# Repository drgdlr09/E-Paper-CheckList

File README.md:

# E-Paper CheckList - A Brief Overview
For the final week of Half-Life, I decided to design the E-Paper CheckList, a simple to-do list device with a 2.9" e-paper screen and three buttons. As a student with a lot of my plate right now, I built the CheckList in order to stay more organized and make sure I get everything I need to do done. I chose e-paper over other types of screens because it keeps showing the list even with no power, meaning the device is power-efficient and can last for a long time on one charge. You can scroll through the list using the buttons and check off items as you complete them.

# How it Works
The E-Paper Checklist has a XIAO ESP32-S3 microcontroller, a 2.9" e-paper screen for showing the list, three buttons (UP, OK and DOWN) for moving through the list and checking items off, a LiPo battery with an SS12D00 on/off switch, and a voltage divider for reading the battery level.

The E-Paper Checklist is built around the Seeed XIAO ESP32-S3, the same microcontroller I used in my Virtual SandBox. I picked it because it has a built-in battery charger and a deep sleep mode that uses almost nearly no power.

The buttons each have a 10k pull-up resistor and are wired between a GPIO pin and ground. The UP button is on D0, OK is on D1, and DOWN is on D2. I put them on these pins on purpose, because only certain pins can wake the ESP32 from deep sleep. UP and DOWN move the highlight through the list, and OK checks or unchecks the highlighted item. Holding DOWN for 1.5 seconds unchecks everything so I can start over the next day.

The e-paper screen talks to the XIAO over SPI. The screen’s SCL pin goes to D8, SDA goes to D10, CS goes to D4, DC goes to D5, RES goes to D6, and BUSY goes to D7. The screen solders straight onto a 1x8 header on the front of the board, so I don’t need any wires. The screen shows up to 6 items per page, with a header that shows how many items are done and the battery percentage.

The battery is set up the same way as my Virtual SandBox. The positive wire goes into the BAT+IN pad, through the on/off switch, out the BAT+OUT pad, and then by wire to the BAT+ pad under the XIAO. The negative wire goes straight to BAT-. The XIAO charges the battery when it’s plugged into USB-C. Two 100k resistors cut the battery voltage in half so D3 can read it, which is how the screen shows the battery percentage. The resistors are after the switch, so they don’t drain the battery when it’s turned off.

# The Firmware
The firmware is written in Arduino C++ and uses the GxEPD2 library for the e-paper screen. After 4 seconds with no button presses, the device will enter sleep mode. Pressing any button will automatically take the device out of sleep mode. The button you press to exit sleep mode matters because as soon as you press that button, the associated action will be triggered automatically.

The list is hardcoded in the firmware, so it is not editable until you change the actual code. In the future, I want to create some sort of app or webpage that allows you to update a schedule from another device, like a smartphone.

# Bill of Materials
| Part | Quantity | Unit Price | Total | Vendor |
| --- | --- | --- | --- | --- |
| 3.7V LiPo Battery | 1 | 1.06 | 1.06 | AliExpress |
| XIAO ESP32-S3 | 1 | 6.83 | 6.83 | AliExpress |
| 2.9" E-Paper Screen | 1 | 14.22 | 14.22 | AliExpress |
| PCB | 1 | 1.75 | 1.75 | JLCPCB |

TOTAL PRICE (INCLUDING $6.56 SHIPPING/TAX): $30.42
*NOTE: Other parts are needed for this project (buttons, capacitors, resistors, switches), but I either already have them or will have extras after purchasing them as part of another week.

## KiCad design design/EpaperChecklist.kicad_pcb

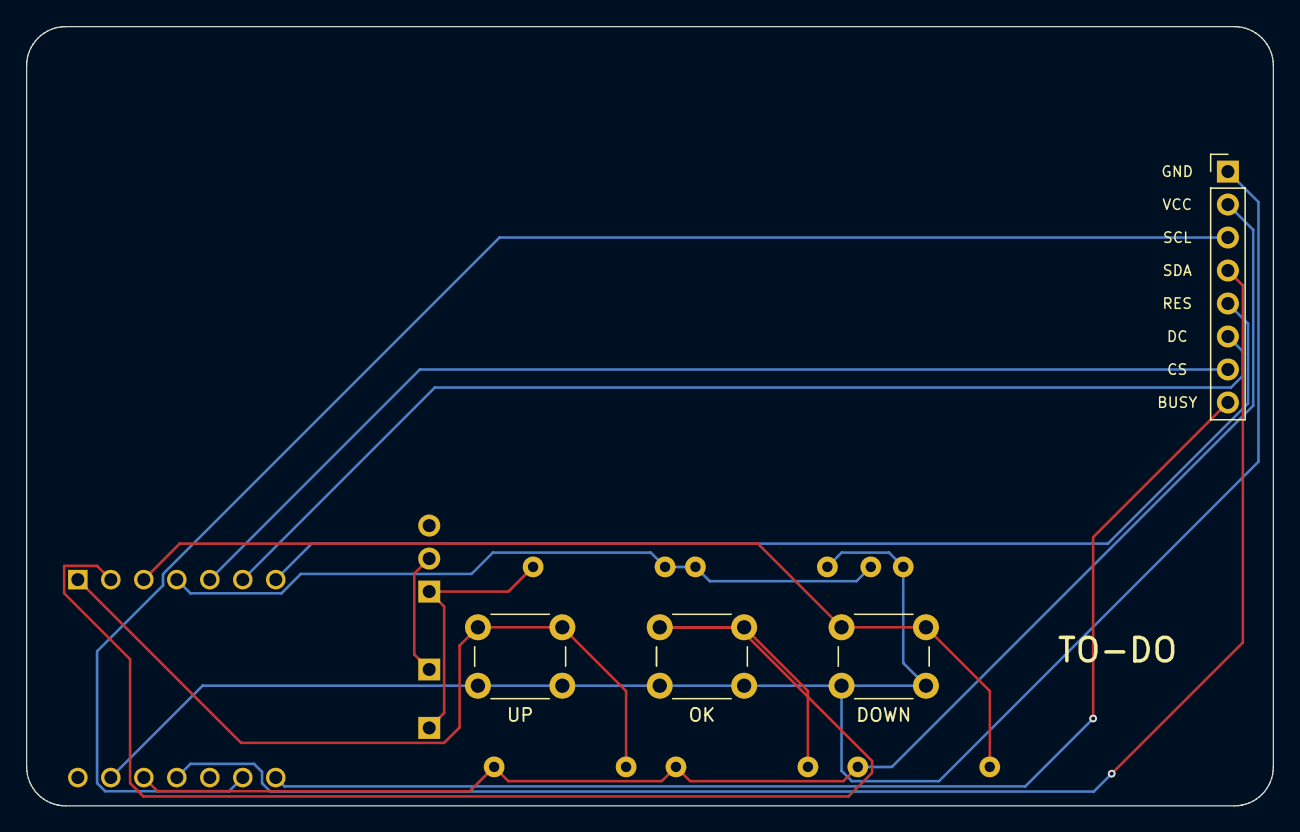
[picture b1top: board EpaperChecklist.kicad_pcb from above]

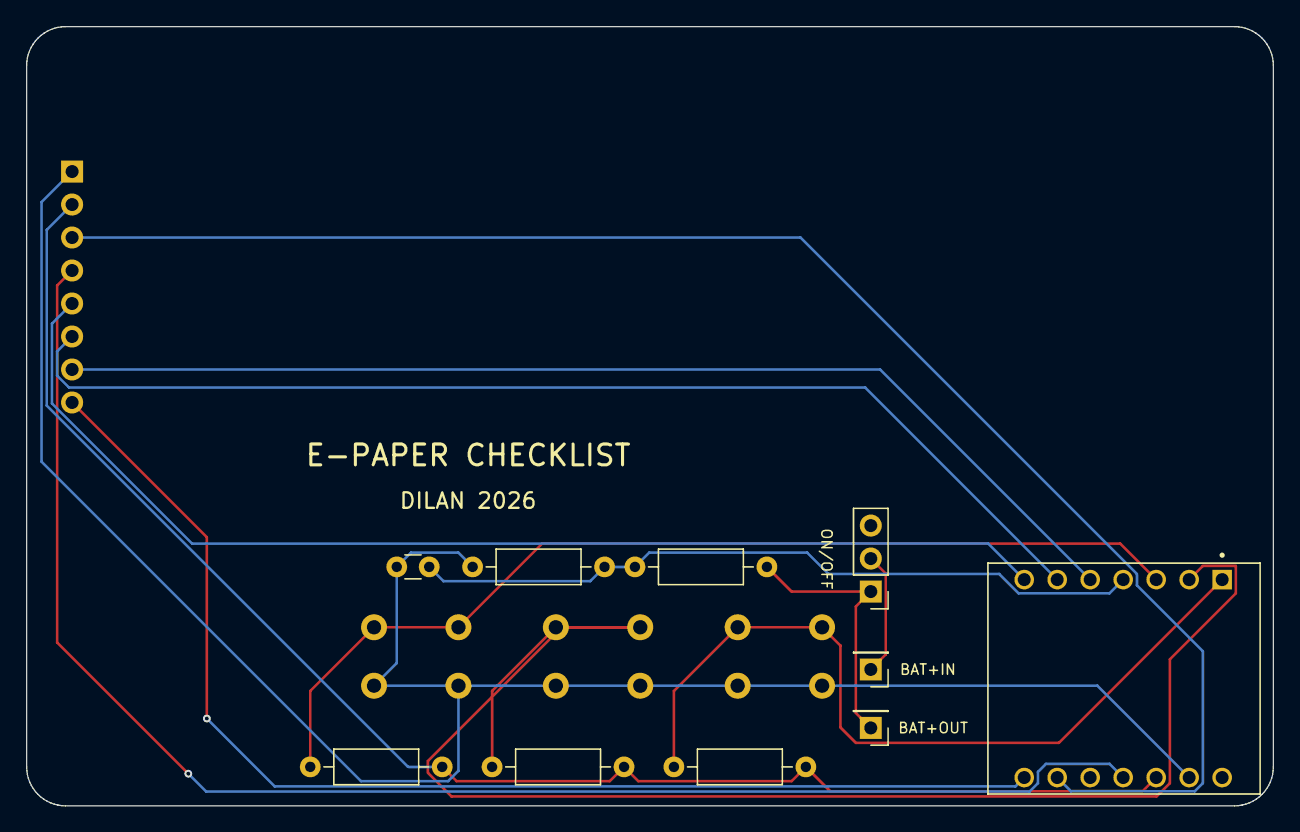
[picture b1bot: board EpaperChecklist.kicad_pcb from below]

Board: 2 copper layers, 96.0 x 60.0 mm, 14 parts (10 on the bottom side), 14 nets.

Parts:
C1: 100nF; C_Disc_D3.0mm_W1.6mm_P2.50mm
J1: E-paper; PinHeader_1x08_P2.54mm_Vertical
J2: BAT+IN; PinHeader_1x01_P2.54mm_Vertical
J3: BAT+OUT; PinHeader_1x01_P2.54mm_Vertical
R1, R2: 100k; R_Axial_DIN0207_L6.3mm_D2.5mm_P10.16mm_Horizontal
R3, R4, R5: 10k; R_Axial_DIN0207_L6.3mm_D2.5mm_P10.16mm_Horizontal
SW1: SS12D00; PinHeader_1x03_P2.54mm_Vertical
SW2: UP; SW_PUSH_6mm
SW3: OK; SW_PUSH_6mm
SW4: DOWN; SW_PUSH_6mm
U1: XIAO-ESP32-S3; XIAO ESP32-S3

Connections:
+3V3: J1.2, R3.1, R4.1, R5.1, U1.12
BAT_ADC: C1.1, R1.2, R2.1, U1.4
BAT_IN: J2.1, SW1.2
BAT_OUT: J3.1, R1.1, SW1.1
BTN_DOWN: R5.2, SW4.1, U1.3
BTN_OK: R4.2, SW3.1, U1.2
BTN_UP: R3.2, SW2.1, U1.1
EPD_BUSY: J1.8, U1.8
EPD_CS: J1.7, U1.5
EPD_DC: J1.6, U1.6
EPD_MOSI: J1.4, U1.11
EPD_RST: J1.5, U1.7
EPD_SCK: J1.3, U1.9
GND: C1.2, J1.1, R2.2, SW2.2, SW3.2, SW4.2, U1.13

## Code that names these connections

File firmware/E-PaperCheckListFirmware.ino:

#include <SPI.h>
#include <GxEPD2_BW.h>
#include <Fonts/FreeSans9pt7b.h>
#include <Fonts/FreeSansBold9pt7b.h>
#include <Preferences.h>

#define EPD_CLASS GxEPD2_290_T94_V2

#define PIN_UP    1
#define PIN_OK    2
#define PIN_DOWN  3
#define PIN_BAT   4
#define EPD_CS    5
#define EPD_DC    6
#define EPD_RST   43
#define EPD_BUSY  44
#define EPD_SCK   7
#define EPD_MOSI  9

#define ROWS       6
#define ROW_H      17
#define TOP        22
#define AWAKE_MS   4000
#define HOLD_MS    1500
#define FULL_EVERY 15

const char *items[] = 
{
  "Finish homework",
  "Study for physics test",
  "Watch a video",
  "Work on devlog",
  "Make Bill of Materials",
  "Reply to emails",
  "Pack backpack",
  "Finish reading article",
  "Take out the recycling",
  "Make bed"
};
const int itemCount = sizeof(items) / sizeof(items[0]);

GxEPD2_BW<EPD_CLASS, EPD_CLASS::HEIGHT> display(EPD_CLASS(EPD_CS, EPD_DC, EPD_RST, EPD_BUSY));
Preferences prefs;

RTC_DATA_ATTR int sel = 0;
RTC_DATA_ATTR int partialCount = 0;
RTC_DATA_ATTR bool booted = false;

uint32_t doneMask = 0;
bool forceFull = false;
uint32_t lastActive = 0;
const uint8_t BTN[3] = {PIN_UP, PIN_OK, PIN_DOWN};
bool wasDown[3];

void loadDone() 
{
  prefs.begin("list", true);
  int n = prefs.getInt("n", -1);
  doneMask = (n == itemCount) ? prefs.getUInt("done", 0) : 0;
  prefs.end();
}

void saveDone() 
{
  prefs.begin("list", false);
  prefs.putInt("n", itemCount);
  prefs.putUInt("done", doneMask);
  prefs.end();
}

int batteryPercent() 
{
  uint32_t mv = 0;
  for (int i = 0; i < 8; i++) mv += analogReadMilliVolts(PIN_BAT);
  mv = mv / 8 * 2;
  return constrain(map(mv, 3300, 4200, 0, 100), 0, 100);
}

String fit(String s, int maxW) 
{
  int16_t x1, y1;
  uint16_t w, h;
  display.getTextBounds(s, 0, 0, &x1, &y1, &w, &h);
  if (w <= maxW) return s;
  while (s.length() > 1) 
  {
    s.remove(s.length() - 1);
    display.getTextBounds(s + "...", 0, 0, &x1, &y1, &w, &h);
    if (w <= maxW) return s + "...";
  }
  return s;
}

void beginDraw() 
{
  if (!booted || forceFull || partialCount >= FULL_EVERY) 
  {
    display.setFullWindow();
    partialCount = 0;
    forceFull = false;
  } 
  else 
  {
    display.setPartialWindow(0, 0, display.width(), display.height());
    partialCount++;
  }
  booted = true;
}

void drawList() 
{
  int bat = batteryPercent();
  int doneCount = __builtin_popcount(doneMask);
  int first = (sel / ROWS) * ROWS;
  int pages = (itemCount + ROWS - 1) / ROWS;
  beginDraw();
  display.firstPage();
  do 
  {
    display.fillScreen(GxEPD_WHITE);
    display.setTextColor(GxEPD_BLACK);
    display.setFont(&FreeSansBold9pt7b);
    display.setCursor(6, 15);
    display.print("TO-DO");
    display.setFont(&FreeSans9pt7b);
    String info = String(doneCount) + "/" + String(itemCount) + " done";
    if (pages > 1) info += "   pg " + String(first / ROWS + 1) + "/" + String(pages);
    display.setCursor(80, 15);
    display.print(info);
    String b = String(bat) + "%";
    int16_t x1, y1;
    uint16_t w, h;
    display.getTextBounds(b, 0, 0, &x1, &y1, &w, &h);
    display.setCursor(display.width() - w - 6, 15);
    display.print(b);
    display.drawLine(0, 19, display.width(), 19, GxEPD_BLACK);

    for (int r = 0; r < ROWS; r++) 
    {
      int i = first + r;
      if (i >= itemCount) break;
      int y = TOP + r * ROW_H;
      bool done = doneMask & (1UL << i);
      uint16_t fg = GxEPD_BLACK;
      if (i == sel) 
      {
        display.fillRect(0, y, display.width(), ROW_H, GxEPD_BLACK);
        fg = GxEPD_WHITE;
      }
      display.drawRect(6, y + 3, 11, 11, fg);
      if (done) display.fillRect(8, y + 5, 7, 7, fg);
      display.setTextColor(fg);
      String t = fit(items[i], display.width() - 32);
      display.setCursor(24, y + 13);
      display.print(t);
      if (done) 
      {
        display.getTextBounds(t, 0, 0, &x1, &y1, &w, &h);
        display.drawLine(24, y + 8, 24 + w, y + 8, fg);
      }
    }
  } while (display.nextPage());
}

void waitRelease(uint8_t pin) 
{
  while (digitalRead(pin) == LOW) delay(10);
  delay(30);
}

bool isHold(uint8_t pin, uint32_t start) 
{
  while (digitalRead(pin) == LOW) 
  {
    if (millis() - start >= HOLD_MS) return true;
    delay(10);
  }
  return false;
}

void handle(uint8_t pin, uint32_t start) 
{
  if (pin == PIN_UP) 
  {
    sel = (sel + itemCount - 1) % itemCount;
    drawList();
  } 
  else if (pin == PIN_OK) 
  {
    doneMask ^= 1UL << sel;
    saveDone();
    drawList();
    waitRelease(pin);
  } 
  else if (isHold(pin, start)) 
  {
    doneMask = 0;
    saveDone();
    drawList();
    waitRelease(pin);
  } 
  else 
  {
    sel = (sel + 1) % itemCount;
    drawList();
  }
  lastActive = millis();
}

void goToSleep() 
{
  display.hibernate();
  uint64_t mask = (1ULL << PIN_UP) | (1ULL << PIN_OK) | (1ULL << PIN_DOWN);
  esp_sleep_enable_ext1_wakeup(mask, ESP_EXT1_WAKEUP_ANY_LOW);
  esp_deep_sleep_start();
}

void setup() 
{
  for (int i = 0; i < 3; i++) pinMode(BTN[i], INPUT_PULLUP);
  SPI.begin(EPD_SCK, -1, EPD_MOSI, EPD_CS);
  display.init(0, !booted, 2, false);
  display.setRotation(1);
  loadDone();
  if (sel >= itemCount) sel = 0;

  if (esp_sleep_get_wakeup_cause() == ESP_SLEEP_WAKEUP_EXT1) 
  {
    uint64_t s = esp_sleep_get_ext1_wakeup_status();
    if (s & (1ULL << PIN_UP)) handle(PIN_UP, 0);
    else if (s & (1ULL << PIN_OK)) handle(PIN_OK, 0);
    else if (s & (1ULL << PIN_DOWN)) handle(PIN_DOWN, 0);
    else drawList();
  } 
  else 
  {
    forceFull = true;
    drawList();
  }

  for (int i = 0; i < 3; i++)
    wasDown[i] = digitalRead(BTN[i]) == LOW;
  lastActive = millis();
}

void loop() 
{
  for (int i = 0; i < 3; i++) {
    bool down = digitalRead(BTN[i]) == LOW;
    if (down && !wasDown[i]) {
      delay(20);
      if (digitalRead(BTN[i]) == LOW) handle(BTN[i], millis());
    }
    wasDown[i] = digitalRead(BTN[i]) == LOW;
  }
  if (millis() - lastActive > AWAKE_MS) goToSleep();
  delay(5);
}
